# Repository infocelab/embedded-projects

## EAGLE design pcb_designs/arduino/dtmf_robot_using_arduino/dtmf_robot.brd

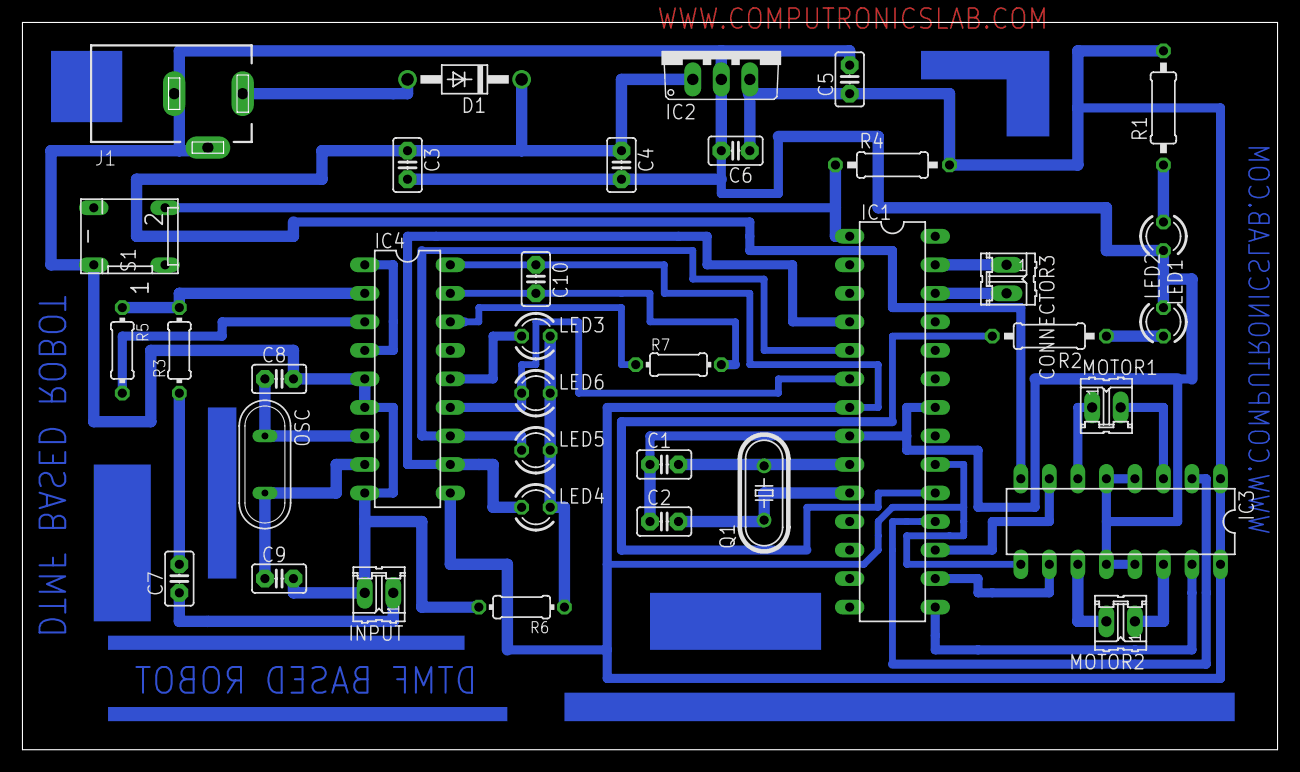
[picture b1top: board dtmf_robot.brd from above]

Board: 2 copper layers, 111.8 x 64.8 mm, 36 parts (0 on the bottom side), 34 nets.

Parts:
C1, C2: 22pf; C2.5-2
C3: 470uF; C2.5-2
C4, C5: 0.1uf; C2.5-2
C6: 4.7uf; C2.5-2
C7: 0.47uf; C2.5-2
C8, C9: 22PF; C2.5-2
C10: 0.1UF; C2.5-2
CONNECTOR3: 02P
D1: 1N4007; DO41-10
IC1: ATMEGA328; DIL28-3
IC2: 7805; TO220V
IC3: L293D; DIL16
IC4: CM8870CP; DIL18
INPUT: 02P
J1: DCJ0303
LED1, LED2, LED3, LED4, LED5, LED6: 3mm; LED3MM
MOTOR1, MOTOR2: 02P
OSC: 3.57; QS
Q1: 16MHZ; HC49/S
R1: 220R; 0207/10
R2: 330R; 0207/10
R3: 10K; 0204/7
R4: 10K; 0207/10
R5, R7: 100K; 0204/7
R6: 330E; 0204/7
S1: push switch; DP-02

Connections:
unnamed: C1.2, IC1.9, Q1.2
unnamed: C2.2, IC1.10, Q1.1
unnamed: D1.A, J1.1
unnamed: C3.1, C4.1, D1.C, IC2.1, IC3.8
unnamed: C1.1, C2.1, C3.2, C4.2, C5.2, C6.2, C8.2, C9.2, IC1.8, IC1.22, IC2.2, IC3.4, IC3.5, IC3.12, IC3.13, IC4.5, IC4.6, IC4.9, INPUT.2, J1.2, J1.3, LED1.K, LED2.K, R6.2, S1.4
unnamed: LED1.A, R1.1
unnamed: IC1.17, IC3.7
unnamed: IC1.4, IC4.11, LED4.A
unnamed: IC1.5, IC4.12, LED5.A
unnamed: IC1.6, IC4.13, LED6.A
unnamed: IC4.14, LED3.A
unnamed: CONNECTOR3.1, IC1.27
unnamed: CONNECTOR3.2, IC1.26
unnamed: IC1.18, IC3.2
unnamed: IC1.15, IC3.15
unnamed: C7.2, R3.1
unnamed: IC1.16, IC3.10
unnamed: C10.2, IC4.17, R7.2
unnamed: IC3.14, MOTOR2.1
unnamed: IC1.19, R2.2
unnamed: IC3.11, MOTOR2.2
unnamed: IC1.1, R4.1, S1.2
unnamed: LED2.A, R2.1
unnamed: IC3.6, MOTOR1.1
unnamed: IC3.3, MOTOR1.2
unnamed: LED3.K, LED4.K, LED5.K, LED6.K, R6.1
unnamed: C5.1, C6.1, C10.1, IC1.7, IC1.20, IC2.3, IC3.1, IC3.9, IC3.16, IC4.10, IC4.18, R1.2, R4.2
unnamed: C7.1, INPUT.1
unnamed: IC4.2, R3.2, R5.1
unnamed: IC4.1, IC4.4
unnamed: IC4.3, R5.2
unnamed: C8.1, IC4.7, OSC.1
unnamed: C9.1, IC4.8, OSC.2
unnamed: IC4.16, R7.1

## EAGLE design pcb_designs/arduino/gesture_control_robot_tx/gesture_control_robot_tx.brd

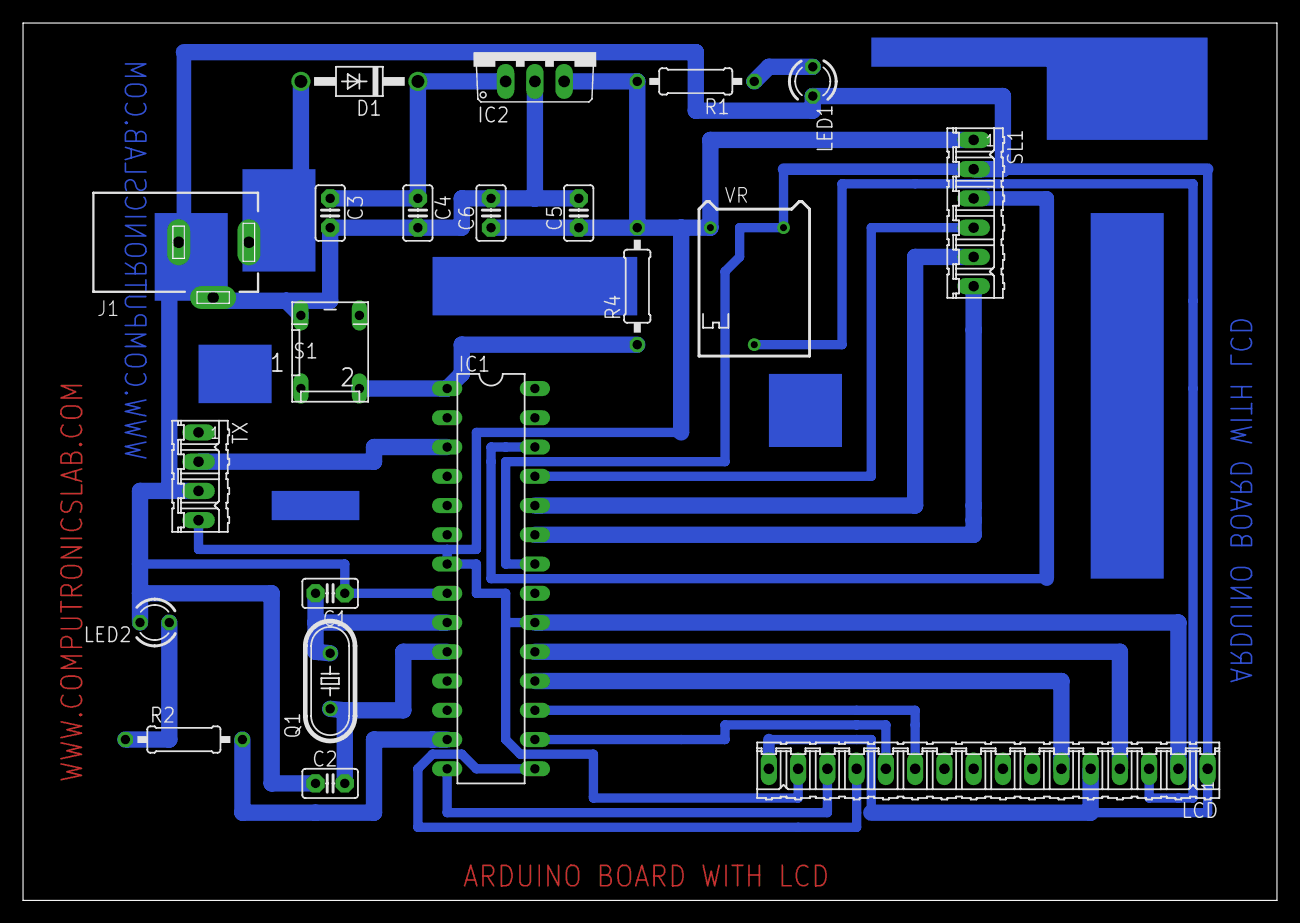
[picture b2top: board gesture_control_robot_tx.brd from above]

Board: 2 copper layers, 108.9 x 76.2 mm, 21 parts (0 on the bottom side), 22 nets.

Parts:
C1, C2: 22pf; C2.5-2
C3: 100UF; C2.5-2
C4, C5: 0.1uf; C2.5-2
C6: 4.7uf; C2.5-2
D1: 1N4007; DO41-10
IC1: ATMEGA328; DIL28-3
IC2: 7805; TO220V
J1: DCJ0303
LCD: 16P
LED1, LED2: LED3MM
Q1: 16MHZ; HC49/S
R1: 220R; 0207/10
R2: 330R; 0207/10
R4: 10K; 0207/10
S1: DP-02
SL1: ACCELEROMETER; 06P
TX: 04P
VR: 100k; RTRIM64P

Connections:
unnamed: C1.2, IC1.9, Q1.2
unnamed: C2.2, IC1.10, Q1.1
unnamed: D1.A, J1.1
unnamed: C5.1, C6.1, IC1.7, IC1.20, IC2.3, LCD.2, LCD.15, R1.2, R4.2, SL1.1, TX.4, VR.1
unnamed: C1.1, C2.1, C3.2, C4.2, C5.2, C6.2, IC1.8, IC1.22, IC2.2, J1.2, J1.3, LCD.1, LCD.5, LCD.16, LED1.K, LED2.K, S1.4, SL1.2, TX.3, VR.3
unnamed: LED1.A, R1.1
unnamed: C3.1, C4.1, D1.C, IC2.1
unnamed: IC1.23, SL1.6
unnamed: IC1.24, SL1.5
unnamed: IC1.25, SL1.4
unnamed: IC1.26, SL1.3
unnamed: IC1.3, TX.2
unnamed: IC1.13, R2.2
unnamed: LCD.3, VR.2
unnamed: IC1.19, LCD.4
unnamed: IC1.18, LCD.6
unnamed: IC1.17, LCD.11
unnamed: IC1.16, LCD.12
unnamed: IC1.15, LCD.13
unnamed: IC1.14, LCD.14
unnamed: IC1.1, R4.1, S1.2
unnamed: LED2.A, R2.1

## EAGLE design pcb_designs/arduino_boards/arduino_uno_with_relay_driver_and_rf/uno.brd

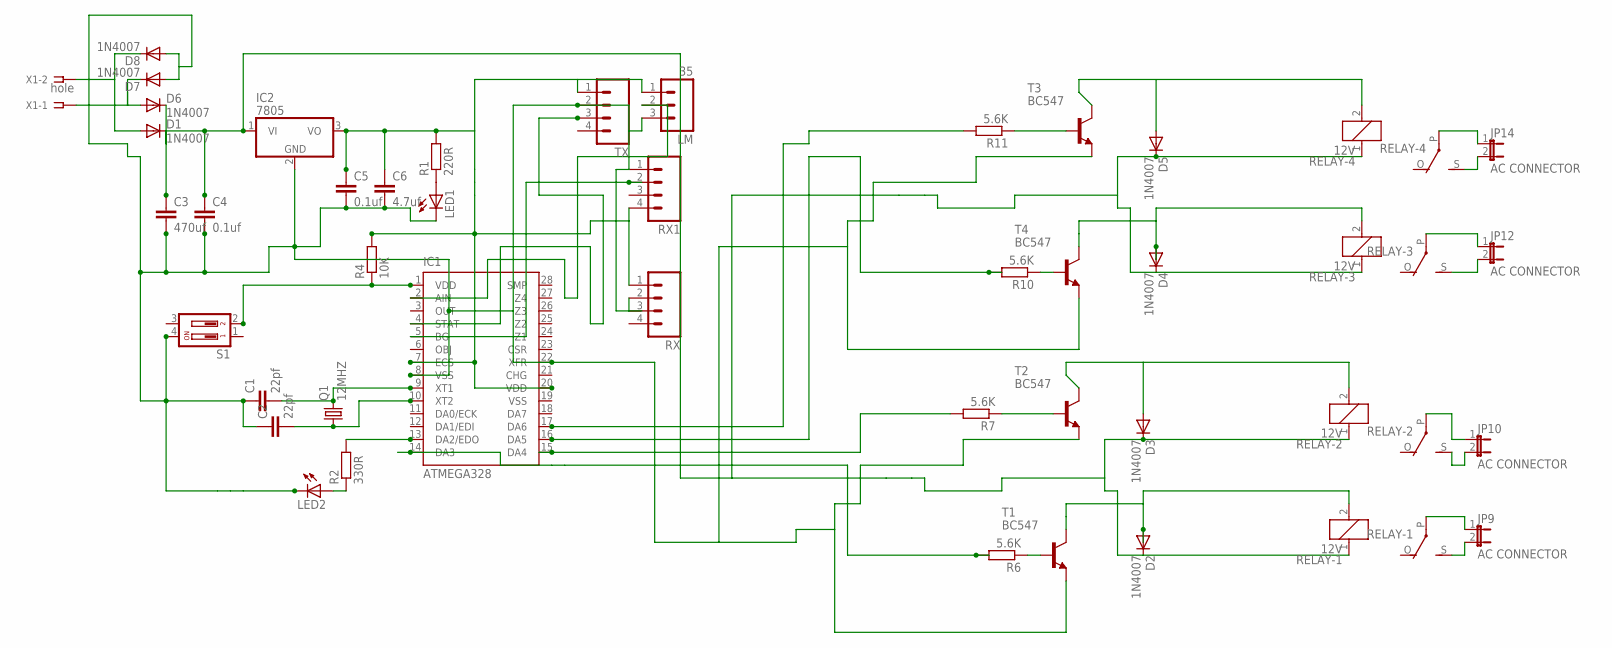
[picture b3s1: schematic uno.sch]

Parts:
C1, C2: 22pf; C2.5-2
C3: 470uf; C2.5-2
C4, C5: 0.1uf; C2.5-2
C6: 4.7uf; C2.5-2
D1, D2, D3, D4, D5, D6, D7, D8: 1N4007; DO41-10
IC1: ATMEGA328; DIL28-3
IC2: 7805; TO220V
JP9, JP10, JP12, JP14: AC CONNECTOR; JP1
LED1, LED2: LED3MM
LM: 35; 03P
Q1: 12MHZ; HC49/S
R1: 220R; 0207/10
R2: 330R; 0207/10
R4: 10K; 0207/10
R6, R7, R10, R11: 5.6K; 0204/7
RELAY-1, RELAY-2, RELAY-3, RELAY-4: 12V; G5LE
RX, RX1: M04; 04P
S1: DP02; DP-02
T1, T2, T3, T4: BC547; TO92
TX: M04; 04P
X1: hole; SSW-101-02-S-D

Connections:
unnamed: C1.2, IC1.9 (XT1), Q1.2
unnamed: C2.2, IC1.10 (XT2), Q1.1
unnamed: C5.1, C6.1, IC1.7 (ECS), IC1.20 (VDD), IC2.3 (VO), LM.1, R1.2, R4.2, RX.1, RX1.4, TX.1
unnamed: LED1.A, R1.1
unnamed: C3.1, C4.1, D1.C, D2.C, D3.C, D4.C, D5.C, D6.C, IC2.1 (VI), RELAY-1.1, RELAY-2.1, RELAY-3.1, RELAY-4.1
unnamed: IC1.2 (AIN), LM.2
unnamed: IC1.5 (BG), RX1.2
unnamed: D6.A, D7.C, X1.1
unnamed: IC1.4 (STAT), TX.3
unnamed: D1.A, D8.C, X1.2
unnamed: IC1.13 (DA2/EDO), R2.2
unnamed: D2.A, RELAY-1.2, T1.3 (C)
unnamed: R7.1, T2.2 (B)
unnamed: R6.1, T1.2 (B)
unnamed: IC1.1 (VDD), R4.1, S1.2
unnamed: LED2.A, R2.1
unnamed: JP9.2, RELAY-1.S
unnamed: JP9.1, RELAY-1.P
unnamed: JP10.2, RELAY-2.S
unnamed: JP10.1, RELAY-2.P
unnamed: IC1.14 (DA3), R6.2
unnamed: D3.A, RELAY-2.2, T2.3 (C)
unnamed: D4.A, RELAY-3.2, T4.3 (C)
unnamed: R11.1, T3.2 (B)
unnamed: R10.1, T4.2 (B)
unnamed: JP12.2, RELAY-3.S
unnamed: JP12.1, RELAY-3.P
unnamed: JP14.2, RELAY-4.S
unnamed: JP14.1, RELAY-4.P
unnamed: C1.1, C2.1, C3.2, C4.2, C5.2, C6.2, D7.A, D8.A, IC1.8 (VSS), IC1.22 (XFR), IC2.2 (GND), LED1.K (C), LED2.K (C), LM.3, RX.2, RX1.1, S1.4, T1.1 (E), T2.1 (E), T3.1 (E), T4.1 (E), TX.2
unnamed: IC1.16 (DA5), R10.2
unnamed: IC1.17 (DA6), R11.2
unnamed: D5.A, RELAY-4.2, T3.3 (C)
unnamed: IC1.15 (DA4), R7.2

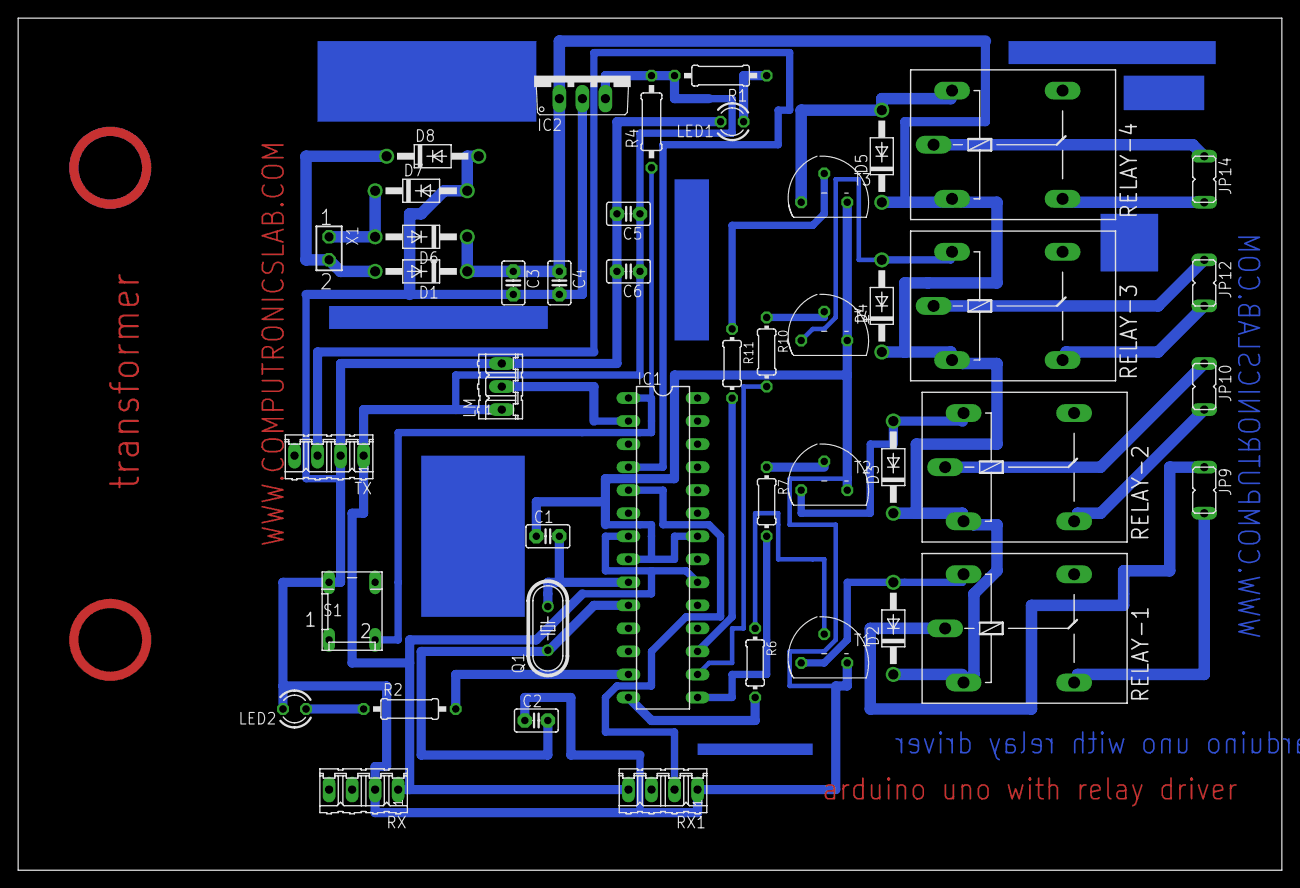
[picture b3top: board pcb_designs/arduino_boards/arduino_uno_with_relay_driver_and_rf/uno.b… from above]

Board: 2 copper layers, 139.4 x 94.0 mm, 44 parts (0 on the bottom side), 34 nets.

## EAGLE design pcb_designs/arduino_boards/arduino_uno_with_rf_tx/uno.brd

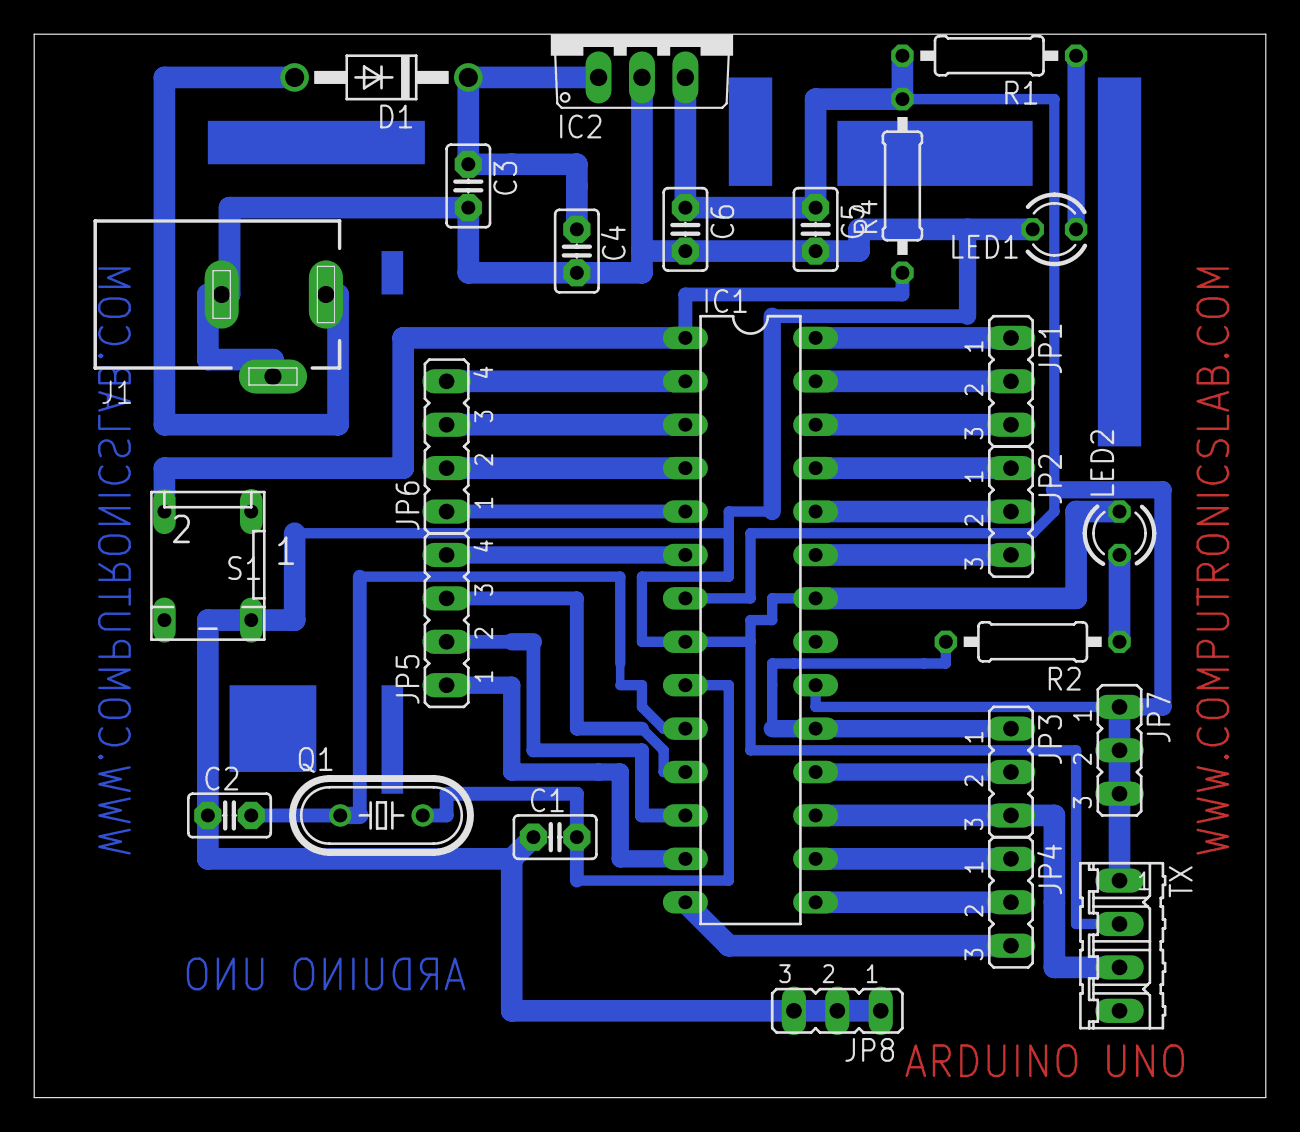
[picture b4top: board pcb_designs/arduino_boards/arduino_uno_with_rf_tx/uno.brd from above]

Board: 2 copper layers, 72.1 x 62.2 mm, 26 parts (0 on the bottom side), 29 nets.

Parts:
C1, C2: 22pf; C2.5-2
C3: 470uF; C2.5-2
C4, C5: 0.1uf; C2.5-2
C6: 4.7uf; C2.5-2
D1: 1N4007; DO41-10
IC1: ATMEGA328; DIL28-3
IC2: 7805; TO220V
J1: DCJ0303
JP1, JP2, JP3, JP4: 3 pin; JP2
JP5, JP6: 4 pin; JP4
JP7, JP8: JP2
LED1, LED2: 3mm; LED3MM
Q1: 16MHZ; HC49/S
R1: 220R; 0207/10
R2: 330R; 0207/10
R4: 10K; 0207/10
S1: push switch; DP-02
TX: 04P

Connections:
unnamed: C1.2, IC1.9, Q1.2
unnamed: C2.2, IC1.10, Q1.1
unnamed: D1.A, J1.1
unnamed: C5.1, C6.1, IC1.7, IC1.20, IC2.3, JP7.1, JP7.2, JP7.3, R1.2, R4.2, TX.1
unnamed: C1.1, C2.1, C3.2, C4.2, C5.2, C6.2, IC1.8, IC1.22, IC2.2, J1.2, J1.3, JP8.1, JP8.2, JP8.3, LED1.K, LED2.K, S1.4, TX.2
unnamed: LED1.A, R1.1
unnamed: C3.1, C4.1, D1.C, IC2.1
unnamed: IC1.28, JP1.1
unnamed: IC1.27, JP1.2
unnamed: IC1.26, JP1.3
unnamed: IC1.25, JP2.1
unnamed: IC1.24, JP2.2
unnamed: IC1.23, JP2.3
unnamed: IC1.5, JP6.1
unnamed: IC1.2, JP6.4
unnamed: IC1.3, JP6.3
unnamed: IC1.4, JP6.2
unnamed: IC1.6, JP5.4
unnamed: IC1.12, JP5.2
unnamed: IC1.11, JP5.3
unnamed: IC1.14, JP4.3
unnamed: IC1.15, JP4.2
unnamed: IC1.16, JP4.1
unnamed: IC1.17, JP3.3, TX.3
unnamed: IC1.18, JP3.2
unnamed: IC1.19, JP3.1, R2.2
unnamed: IC1.13, JP5.1
unnamed: IC1.1, R4.1, S1.2
unnamed: LED2.A, R2.1

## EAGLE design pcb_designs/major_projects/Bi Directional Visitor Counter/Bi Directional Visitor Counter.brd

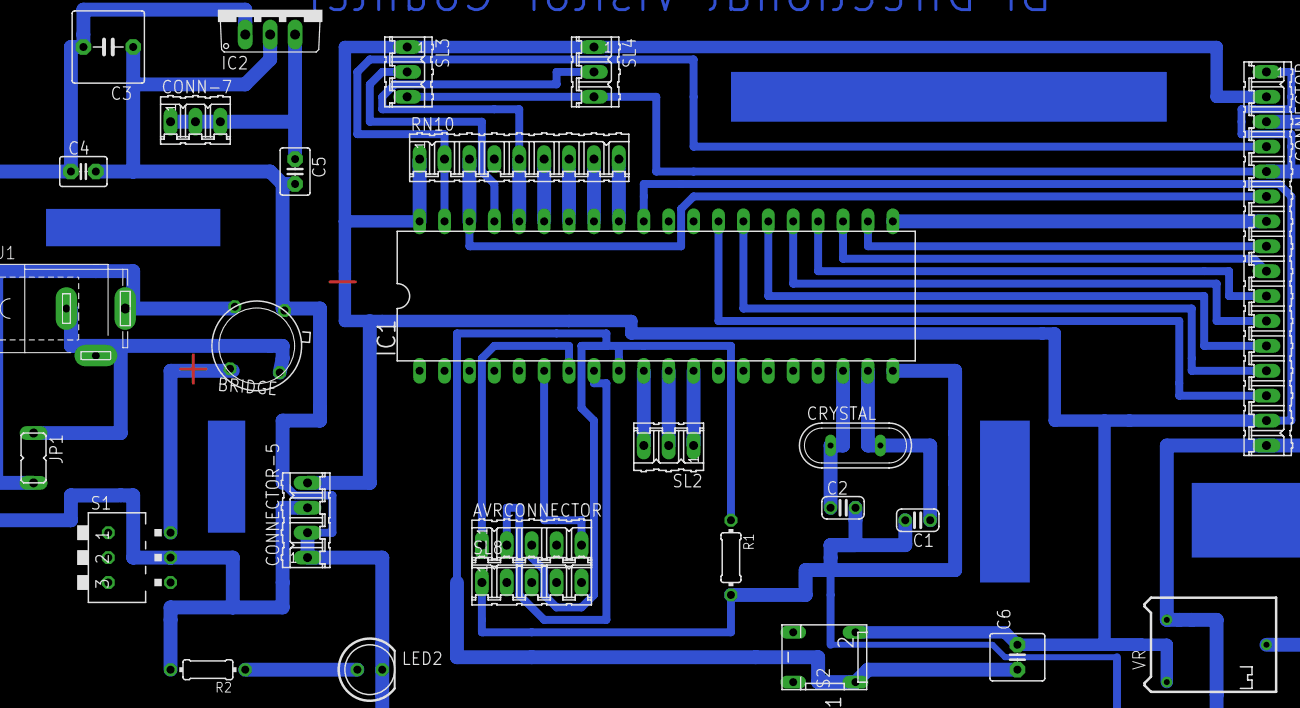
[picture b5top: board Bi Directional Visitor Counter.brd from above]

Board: 2 copper layers, 27 parts (0 on the bottom side), 34 nets.

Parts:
AVRCONNECTOR: 05P
BRIDGE: TO39/4
C1, C2: 33pf; C025-024X044
C3: 470uf; C5B7.2
C4: .01uf; C2.5-3
C5: 4.7uf; C2.5-3
C6: 0.1uf; C2.5-6
CONN-7: 3 pin; 03P
CONNECTOR: LCD; 16P
CONNECTOR-5: 4 pin; 04P
CRYSTAL: 11.0592 mhz; QS
IC1: AT89S51; DIL40
IC2: 7805TV; TO220V
J1: SPC4077
JP1: TRANSFORMER; JP1
LED2: 5mm; LED5MM
R1: 10k; 0204/7
R2: 560E; 0204/7
RN10: 10 k; 09P
S1: ON/ OFF SWITCH; DA-03
S2: push switch; DP-02
SL2: 3 pin; 03P
SL3, SL4: ir module; 03P
SL8: 05P
VR: 10k; RTRIM64P

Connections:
unnamed: C2.1, CRYSTAL.1, IC1.18
unnamed: C1.1, CRYSTAL.2, IC1.19
unnamed: IC1.12, SL2.1
unnamed: C3.2, C4.1, CONNECTOR-5.3, IC2.1, R2.2, S1.5
unnamed: BRIDGE.2, J1.3, JP1.2
unnamed: IC1.11, SL2.2
unnamed: IC1.10, SL2.3
unnamed: C6.2, CONNECTOR.2, CONNECTOR.15, CONNECTOR-5.4, IC1.31, IC1.40, RN10.1, S2.2, SL3.1, SL4.1, VR.1
unnamed: AVRCONNECTOR.3, C6.1, IC1.9, R1.1, S2.1
unnamed: AVRCONNECTOR.1, IC1.7
unnamed: BRIDGE.4, J1.1, J1.2, JP1.1
unnamed: IC1.37, SL3.2
unnamed: IC1.36, RN10.5, SL4.2
unnamed: IC1.35, RN10.6
unnamed: IC1.34, RN10.7
unnamed: IC1.33, RN10.8
unnamed: IC1.32, RN10.9
unnamed: CONNECTOR.7, IC1.21
unnamed: CONNECTOR.8, IC1.22
unnamed: CONNECTOR.9, IC1.23
unnamed: CONNECTOR.12, IC1.26
unnamed: CONNECTOR.3, VR.2
unnamed: C5.1, CONN-7.1, CONN-7.2, CONN-7.3, IC2.3
unnamed: BRIDGE.1, C1.2, C2.2, C3.1, C4.2, C5.2, CONNECTOR.1, CONNECTOR.5, CONNECTOR.16, CONNECTOR-5.1, CONNECTOR-5.2, IC1.20, IC2.2, LED2.K, R1.2, SL3.3, SL4.3, SL8.1, VR.3
unnamed: AVRCONNECTOR.5, IC1.6
unnamed: LED2.A, R2.1
unnamed: AVRCONNECTOR.2, IC1.8
unnamed: BRIDGE.3, S1.6
unnamed: CONNECTOR.6, IC1.38, RN10.3
unnamed: CONNECTOR.10, IC1.24
unnamed: CONNECTOR.11, IC1.25
unnamed: CONNECTOR.13, IC1.27
unnamed: CONNECTOR.14, IC1.28
unnamed: CONNECTOR.4, IC1.39, RN10.2
